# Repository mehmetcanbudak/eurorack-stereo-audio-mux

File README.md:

# stereo audio mixer for eurorack

there are two basic circuit categories to choose from :
* passive
* active

# passive circuit
* single stereo pair mixer - 1 input / 1 output
  * current-limiting resistors on the inputs and outputs (1k ohm)
  * 2 x 9mm rotary vertical pot (100k ohm)
    * Panasonic EVU-F2MFL3D14 [octopart](https://octopart.com/evu-f2mfl3d14-panasonic-39595543?r=sp&s=xV7VNI5JR6W7B-j7famTyw#ecad)
  * 2 x 6.35mm TRS jack connectors

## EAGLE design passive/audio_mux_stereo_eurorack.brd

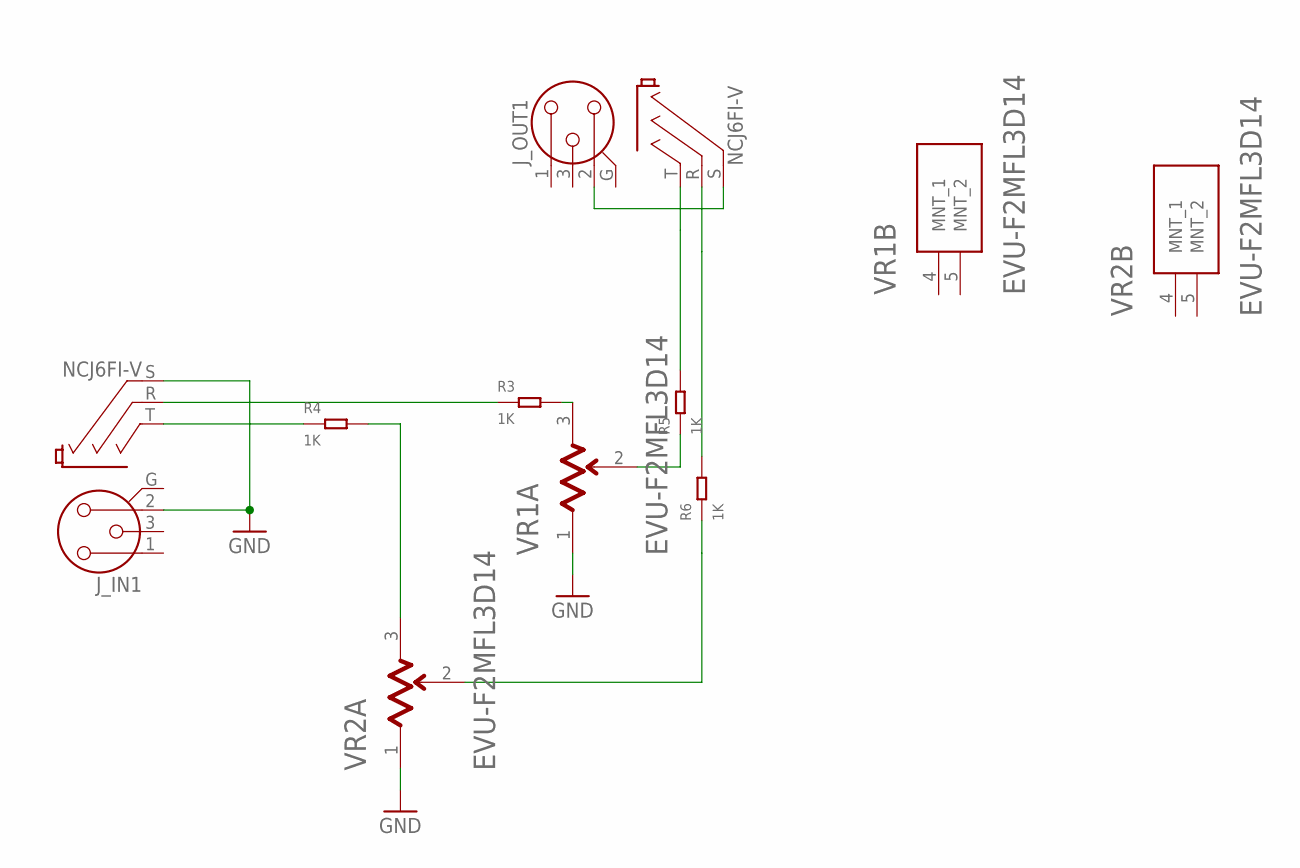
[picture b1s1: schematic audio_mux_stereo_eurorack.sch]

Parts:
J_IN1: NCJ6FI-V
J_OUT1: NCJ6FI-V
R3, R4, R5, R6: 1K; R0805
VR1, VR2: PANASONIC_EVU-F2MFL3D14PANASONIC_EVU-F2MFL3D14_0_0; PANASONIC_EVU-F2MFL3D14_0

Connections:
GND: J_IN1.2, J_IN1.S, VR1.1, VR2.1
unnamed: J_OUT1.R, R6.2
unnamed: J_OUT1.2, J_OUT1.S
unnamed: J_IN1.R, R3.1
unnamed: J_IN1.T, R4.1
unnamed: R3.2, VR1.3
unnamed: R4.2, VR2.3
unnamed: R5.1, VR1.2
unnamed: R6.1, VR2.2
unnamed: J_OUT1.T, R5.2

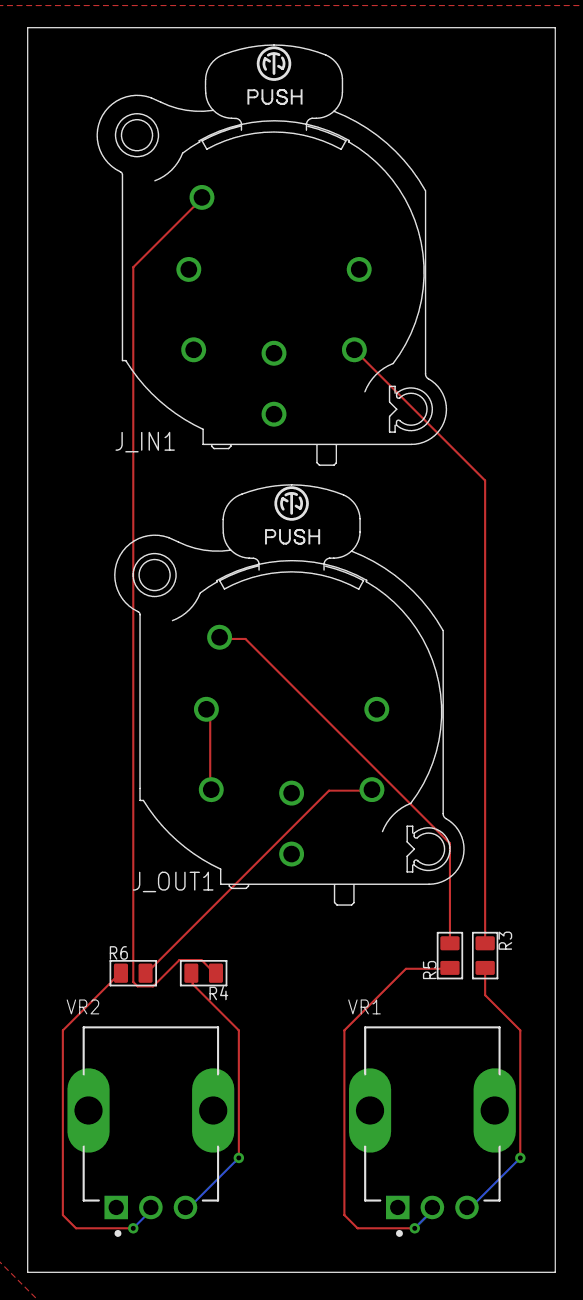
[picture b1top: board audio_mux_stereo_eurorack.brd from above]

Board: 2 copper layers, 38.1 x 89.8 mm, 8 parts (0 on the bottom side), 10 nets.

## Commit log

2021-02-01 [ImgBot] Optimize images
    /passive/images/audio_mixer_1x1_passive.png -- 43.38kb -> 10.12kb (76.68%)
